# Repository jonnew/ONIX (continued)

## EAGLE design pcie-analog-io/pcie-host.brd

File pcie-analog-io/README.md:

# analog IO card

This board roughly conforms the PCIe card mechanical standard and uses a flex
FMC cable to connect to the master FPGA module. This board performs all
communication over FMC -- the PCIe slot design is for mechanical support and to
provide a common and standardized mounting solution across acquisition PCs

### Features

- 16 chs ADC
- 16 chs DAC
- Digital io

### Pinout

Conform to standard NI high density VHDCI pinouts to enable the use of existing cables and breakout boxes

### BOM

#### ADC

AD7616BSTZ-ND

http://www.ti.com/lit/ds/symlink/ads7950.pdf

http://www.analog.com/en/products/analog-to-digital-converters/precision-adc-20msps/simultaneous-sampling-ad-converters/ad7617.html?doc=AD7617.pdf

#### DAC

http://www.analog.com/en/products/digital-to-analog-converters/precision-dac/bipolar-da-converters/ad5767.html

http://www.analog.com/en/products/digital-to-analog-converters/precision-dac/bipolar-da-converters/ad5767.html

LTC2668CUJ-12#PBF-ND

296-25558-1-ND

#### Isolation
I dont think this is needed

#### LVDS to single ended

#### Connector

We can use Molex dual/stacked Ultra+(tm) VHDCI plugs
http://www.molex.com/molex/products/family?key=ultra__vhdci&channel=products&chanName=family&pageTitle=Introduction&parentKey=shielded_input_output_io

We likely have enough space to fit two of these on there (~44mm width each) 

## Manufacturing requirements

TODO:
- PCB thickness:
- 4 layers
- 8mil trace width & spacing
- 12mil min. drill

PCI Brackets:
http://www.mouser.com/Search/ProductDetail.aspx?R=9203virtualkey53400000virtualkey534-9203
http://www.cbttechnology.com/products/s/PCI/PCI-blanks-database.php
http://www.keyelco.com/category.cfm/Standard-Blanks/Computer-Bracket-Blanks-With-Tabs/p/427/id/704/c_id/899

There is one 0.05" pitch BGA connector (the samtech FMC connector) and a few omnetics connectors with inacessible pins on the board, so a stencil and reflow soldering need to be used.

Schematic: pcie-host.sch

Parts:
C1: 1uF; 0603
C2, C5, C6, C7, C8, C9, C17, C25, C39, C40, C49, C50, C51, C52, C53, C54, C55, C56, C57, C58, C59, C60, C61, C80, C81, C82, C84, C86, C88, C91, C92, C93, C95, C97: 0.1uF; 0603
C3, C13: 4.7uF; 0805
C4: 10uF; 0603
C10, C11, C26, C27, C28, C30, C31, C32, C33: 10nF; 0402
C12: 47nF; 0402
C14, C15, C16, C23, C29, C34, C35, C36, C37: 0.1uF; 0402
C18, C22, C38: 4.7uF; 1206
C19: 4.7F; 1206
C20: 1uF; 0805
C21, C24: 22uF; 1206
C42, C45: 10uF; 1206
C44: 100uF; 153CLV-0807
C46: 47uF; 153CLV-0807
C47, C48, C66, C87: 22uF; 1210-POL
C83, C85, C89, C90, C94, C96, C98: 1nF; 0402
D1, D2, D3, D4: BAR66; SOT23
D5: LM4040D25FTA; SOT23
D6: KDZ4.3B; SOD123
DI1, DI2: SMA002; SMA_JACK_CONREVSMA002-G
DO1, DO2: SMA002; SMA_JACK_CONREVSMA002-G
F1, F2, F3, F4: C014F-2; 1812
FMC_LPC: FMC_LPC_160_PIN; FMC_LPC_MALE_WITH_SP601_BSILK
L1: 1008PS-472KLB; 1008PS
L2: SRN6045TA-101M; SRN6045TA
L3: MPZ2012S102AT000; 0805
L4, L5, L6: BLM18KG601SN1D; 0603
L7/0R: 74438356010; 4020
LINK: SMA002; SMA_JACK_CONREVSMA002-G
OUT: 569-011x; 569-011X-X00_LED_ARRAY
PCIE-PWR: 0455580003; PCIE-POWER-6PIN
PWR/LOCK: 569-011x; 569-011X-X00_LED_ARRAY
Q1, Q2, Q5: NDS351AN; SOT23-GSD
Q3, Q4: BSH103; SOT23-GSD
R1, R2, R9, R11, R33, R46, R65, R66, R71, R72, R73, R74, R75: 1k; 0603
R3, R4, R8, R10, R34: 100k; 0603
R5, R6, R31, R32, R69, R70: 2.2k; 0603
R7, R20: 1K; 0603
R12, R13: 4.7k; 0603
R14, R15, R18, R19, R25, R57, R60, R62: 10K; 0402
R16, R17, R21, R22, R23, R24: 150,0.25W; 1206
R26, R27, R56: 10k; 0603
R28, R29, R67: 100; 0603
R30: 49.9; 0402
R35, R36, R37, R38, R39, R40, R41, R42, R43, R44, R45, R47, R48, R49, R50, R51, R52, R53, R54: 22; 0402
R55: 30.1k; 0603
R58, R61, R63: 0; 0402
R59: 13.3k; 0603
R64: 649k; 0603
R68: 9.53k; 0603
TERM: 569-011x; 569-011X-X00_LED_ARRAY
TP1, TP18, TP19, TP20, TP28: GND(ISO); TESTPOINT_1MM
TP2: +1.8V(ISO); TESTPOINT_1MM
TP3: +3.3V(ISO); TESTPOINT_2MM
TP4: +5.5V(ISO); TESTPOINT_2MM
TP5: PASS; TP06R
TP6: DI1; TP09SQ
TP7: DI0; TP09SQ
TP8: GND; TESTPOINT_0.035IN
TP9: VPROTECT(+4.3V); TESTPOINT_0.035IN
TP10, TP14, TP15, TP16, TP17, TP21: GND; TESTPOINT_2MM
TP11, TP22: +3.3V; TESTPOINT_2MM
TP12: +12V(FPGA); TESTPOINT_2MM
TP13: +12V(ATX); TESTPOINT_2MM
TP23: GND; TESTPOINT_1MM
TP24: SDA; TESTPOINT_1MM
TP25: SCL; TESTPOINT_1MM
TP26: SCL(ISO); TESTPOINT_1MM
TP27: SDA(ISO); TESTPOINT_1MM
TP29: GPIO3; TP06R
U1: ISO; SCREW4
U2, U3: JP3E; JP3
U4: SN74LVT125; SO14
U5, U6: ADCMP600; SOT-23-5
U7: DIPSW-004_SMD-0.05IN; DIP04-SMD
U8: MCP47FEBX2; TSSOP-8
U9: DS90UB914A-Q1; WQFN48
U10: LTM4622_BGA; BGA_5X5_625X625
U11: ISO1540DR; SOIC127P500X400-8N
U12: UEI15-050-Q12P-C; UEI15
U13, U14, U15, U16: ISO7240M; SOIC_WIDE_16
U17: ISO7242M; SOIC_WIDE_16
U18: COMM; SCREW4
U19: SN65LVDT388A; TSSOP-38
U20: SN65LVDS387; TSSOP-64
U21: SN65LVDS391; TSSOP-16
U$2: MOLEX_DUAL_STACKED_VHDCI; MOLEX_743370911_SD_DUAL_STACKED_VHDCI
X1: PCI-MECH_STD-H_HALF-W_FMC-STRAIN; PCI-ADDIN_STD-H_HALF-L_FMC-STRAIN

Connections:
2V5_REF: D5.1 (C), R67.1, U2.3, U3.3
$N1: D4.3 (COMM), F2.2, R6.2, R17.2, R22.2, R24.2, R29.1
$N2: D2.3 (COMM), F4.2, R12.2, U4.8 (3Y), U4.11 (4Y)
$N3: D3.3 (COMM), F1.2, R5.2, R16.2, R21.2, R23.2, R28.1
$N101: D1.3 (COMM), F3.2, R13.2, U4.3 (1Y), U4.6 (2Y)
+1V8_ISO: C24.2, C31.2, C32.2, C33.2, C35.2, C36.2, C37.2, L4.2, L5.2, L6.1, R57.1, R60.1, R62.1, TP2.1, U1.2, U9.3 (VDDSSCG), U9.17 (VDDD), U9.36 (VDDR), U10.D1 (VOUT1), U10.E1 (VOUT1)
+3V3: C1.2, C2.2, C8.1, C9.1, C20.2, C25.2, C56.2, C57.2, C58.2, C59.2, C60.2, C61.2, C81.2, C83.2, C84.2, C85.2, C86.2, C87.+, C88.2, C89.2, C90.2, C91.2, C92.2, C93.2, C94.2, C95.2, C96.2, C97.2, C98.2, FMC_LPC.P$116 (3P3V2), FMC_LPC.P$118 (3P3V3), FMC_LPC.P$120 (3P3V4), FMC_LPC.P$159 (3P3V1), R1.2, R2.2, R31.2, R32.2, R67.2, R71.2, R72.2, TP11.1, TP22.1, U4.14 (VCC), U5.5 (V+), U6.5 (V+), U8.1 (VDD), U8.2 (REFA), U11.1 (VDD1), U13.P10 (EN2), U13.P16 (VDD2), U14.P10 (EN2), U14.P16 (VDD2), U15.P10 (EN2), U15.P16 (VDD2), U16.P10 (EN2), U16.P16 (VDD2), U17.P10 (EN2), U17.P16 (VDD2), U18.2, U19.21 (VCC), U19.22 (END), U19.25 (ENC), U19.29 (DVCC), U19.33 (ENB), U19.36 (ENA), U19.37 (VCC), U20.2 (VCC), U20.3 (VCC), U20.5 (ENA), U20.10 (ENB), U20.16 (VCC), U20.17 (VCC), U20.23 (ENC), U20.28 (END), U20.30 (VCC), U20.31 (VCC), U21.1 (EN1,2), U21.4 (VCC), U21.8 (EN3,4)
+3V3_ISO: C21.2, C27.2, C28.2, C29.2, C30.2, C34.2, C38.2, C49.2, C50.2, C51.2, C52.2, C53.2, C54.2, R14.2, R15.2, R18.2, R19.2, R25.1, R46.2, R65.2, R66.2, R75.2, TP3.1, U1.3, U9.7 (VDDIO3), U9.20 (VDDIO2), U9.29 (VDDIO1), U10.A1 (VOUT2), U10.B1 (VOUT2), U11.8 (VDD2), U13.P1 (VDD1), U14.P1 (VDD1), U15.P1 (VDD1), U16.P1 (VDD1), U17.P1 (VDD1)
+3V3_ISO_PG: U16.P11 (VOD), U20.27 (D4A)
+3V3_ISO_PG_ISO: R56.2, U10.D4 (PGOOD1), U16.P6 (VID)
+3V3_ISO_PG_N: FMC_LPC.P$89 (LA01_N_CC), U20.33 (D4Z)
+3V3_ISO_PG_P: FMC_LPC.P$88 (LA01_P_CC), U20.34 (D4Y)
+5.5V_ISO: C13.2, C17.1, C42.2, C45.2, C47.+, C48.+, L3.1, TP4.1, U10.A2 (VIN), U10.B2 (RUN2), U10.B3 (VIN), U10.D2 (RUN1), U10.D3 (VIN), U10.E2 (VIN), U12.3 (+VO)
+12V_ATX: C44.+, C46.+, L7/0R.1, PCIE-PWR.1, PCIE-PWR.2, PCIE-PWR.3, TP13.1
+12V_FPGA: C66.+, C80.2, C82.2, FMC_LPC.P$155 (12P0V1), FMC_LPC.P$157 (12P0V2), R69.2, R70.2, TP12.1, U18.3
BIAS_DI0: U2.1, U8.3 (VOUT0)
BIAS_DI1: U3.1, U8.4 (VOUT1)
BISTEN: R19.1, U7.1, U9.6 (BISTEN)
D0: U13.P14 (VOA), U20.6 (A1A)
D0_ISO: R54.1, U13.P3 (VIA)
D0_N: FMC_LPC.P$98 (LA13_N), U20.63 (A1Z)
D0_P: FMC_LPC.P$97 (LA13_P), U20.64 (A1Y)
D1: U13.P13 (VOB), U20.7 (A2A)
D1_ISO: R38.1, U13.P4 (VIB)
D1_N: FMC_LPC.P$17 (LA11_N), U20.61 (A2Z)
D1_P: FMC_LPC.P$16 (LA11_P), U20.62 (A2Y)
D2: U13.P12 (VOC), U20.8 (A3A)
D2_ISO: R45.1, U13.P5 (VIC)
D2_N: FMC_LPC.P$56 (LA12_N), U20.59 (A3Z)
D2_P: FMC_LPC.P$55 (LA12_P), U20.60 (A3Y)
D3: U13.P11 (VOD), U20.9 (A4A)
D3_ISO: R53.1, U13.P6 (VID)
D3_N: FMC_LPC.P$135 (LA10_N), U20.57 (A4Z)
D3_P: FMC_LPC.P$134 (LA10_P), U20.58 (A4Y)
D4: U14.P14 (VOA), U20.11 (B1A)
D4_ISO: R37.1, U14.P3 (VIA)
D4_N: FMC_LPC.P$95 (LA09_N), U20.55 (B1Z)
D4_P: FMC_LPC.P$94 (LA09_P), U20.56 (B1Y)
D5: U14.P13 (VOB), U20.12 (B2A)
D5_ISO: R44.1, U14.P4 (VIB)
D5_N: FMC_LPC.P$14 (LA07_N), U20.53 (B2Z)
D5_P: FMC_LPC.P$13 (LA07_P), U20.54 (B2Y)
D6: U14.P12 (VOC), U20.13 (B3A)
D6_ISO: R52.1, U14.P5 (VIC)
D6_N: FMC_LPC.P$53 (LA08_N), U20.51 (B3Z)
D6_P: FMC_LPC.P$52 (LA08_P), U20.52 (B3Y)
D7: U14.P11 (VOD), U20.14 (B4A)
D7_ISO: R36.1, U14.P6 (VID)
D7_N: FMC_LPC.P$92 (LA05_N), U20.49 (B4Z)
D7_P: FMC_LPC.P$91 (LA05_P), U20.50 (B4Y)
D8: U15.P14 (VOA), U20.19 (C1A)
D8_ISO: R43.1, U15.P3 (VIA)
D8_N: FMC_LPC.P$11 (LA04_N), U20.47 (C1Z)
D8_P: FMC_LPC.P$10 (LA04_P), U20.48 (C1Y)
D9: U15.P13 (VOB), U20.20 (C2A)
D9_ISO: R51.1, U15.P4 (VIB)
D9_N: FMC_LPC.P$131 (LA06_N), U20.45 (C2Z)
D9_P: FMC_LPC.P$130 (LA06_P), U20.46 (C2Y)
D10: U15.P12 (VOC), U20.21 (C3A)
D10_ISO: R35.1, U15.P5 (VIC)
D10_N: FMC_LPC.P$50 (LA03_N), U20.43 (C3Z)
D10_P: FMC_LPC.P$49 (LA03_P), U20.44 (C3Y)
D11: U15.P11 (VOD), U20.22 (C4A)
D11_ISO: R42.1, U15.P6 (VID)
D11_N: FMC_LPC.P$8 (LA02_N), U20.41 (C4Z)
D11_P: FMC_LPC.P$7 (LA02_P), U20.42 (C4Y)
DAC_LAT: U8.6 (LAT/HVC), U19.32 (B1Y)
DAC_LAT_N: FMC_LPC.P$20 (LA15_N), U19.7 (B1B)
DAC_LAT_P: FMC_LPC.P$19 (LA15_P), U19.6 (B1A)
DI0: TP7.TP, U5.1 (OUT), U21.2 (1A)
DI0_N: FMC_LPC.P$68 (LA25_N), U21.15 (1Z)
DI0_P: FMC_LPC.P$67 (LA25_P), U21.16 (1Y)
DI0_TERM: R9.1, R73.1, U19.35 (A1Y)
DI0_TERM_N: FMC_LPC.P$139 (LA1N_N), U19.2 (A1B)
DI0_TERM_P: FMC_LPC.P$138 (LA14_P), U19.1 (A1A)
DI1: TP6.TP, U6.1 (OUT), U21.3 (2A)
DI1_N: FMC_LPC.P$29 (LA24_N), U21.13 (2Z)
DI1_P: FMC_LPC.P$28 (LA24_P), U21.14 (2Y)
DI1_TERM: R11.1, R74.1, U19.34 (A2Y)
DI1_TERM_N: FMC_LPC.P$59 (LA16_N), U19.4 (A2B)
DI1_TERM_P: FMC_LPC.P$58 (LA16_P), U19.3 (A2A)
DO0: U4.2 (1A), U4.5 (2A), U19.26 (C2Y)
DO0_N: FMC_LPC.P$143 (LA18_N_CC), U19.12 (C1B)
DO0_P: FMC_LPC.P$142 (LA18_P_CC), U19.11 (C1A)
DO1: U4.9 (3A), U4.12 (4A), U19.27 (C1Y)
DO1_N: FMC_LPC.P$62 (LA20_N), U19.14 (C2B)
DO1_P: FMC_LPC.P$61 (LA20_P), U19.13 (C2A)
DOUTP_F: C16.2, L1.2, LINK.CLK (1), R7.2
DO_TEST: U19.31 (B2Y)
DO_TEST_N: FMC_LPC.P$101 (LA17_N_CC), U19.9 (B2B)
DO_TEST_P: FMC_LPC.P$100 (LA17_P_CC), U19.8 (B2A)
GND: C1.1, C2.1, C6.2, C7.2, C8.2, C9.2, C20.1, C25.1, C44.-, C46.-, C55.1, C56.1, C57.1, C58.1, C59.1, C60.1, C61.1, C66.-, C80.1, C81.1, C82.1, C83.1, C84.1, C85.1, C86.1, C87.-, C88.1, C89.1, C90.1, C91.1, C92.1, C93.1, C94.1, C95.1, C96.1, C97.1, C98.1, D1.1 (A), D2.1 (A), D3.1 (A), D4.1 (A), D5.2 (A), D6.A, DI1.GND$1 (2), DI1.GND$2 (2), DI1.GND$3 (2), DI1.GND$4 (2), DI2.GND$1 (2), DI2.GND$2 (2), DI2.GND$3 (2), DI2.GND$4 (2), DO1.GND$1 (2), DO1.GND$2 (2), DO1.GND$3 (2), DO1.GND$4 (2), DO2.GND$1 (2), DO2.GND$2 (2), DO2.GND$3 (2), DO2.GND$4 (2), FMC_LPC.GNDA (GND), FMC_LPC.GNDB (GND), FMC_LPC.P$3 (GND), FMC_LPC.P$6 (GND), FMC_LPC.P$9 (GND), FMC_LPC.P$12 (GND), FMC_LPC.P$15 (GND), FMC_LPC.P$18 (GND), FMC_LPC.P$21 (GND), FMC_LPC.P$24 (GND), FMC_LPC.P$27 (GND), FMC_LPC.P$30 (GND), FMC_LPC.P$33 (GND), FMC_LPC.P$36 (GND), FMC_LPC.P$39 (GND), FMC_LPC.P$41 (GND), FMC_LPC.P$44 (GND), FMC_LPC.P$45 (GND), FMC_LPC.P$48 (GND), FMC_LPC.P$51 (GND), FMC_LPC.P$54 (GND), FMC_LPC.P$57 (GND), FMC_LPC.P$60 (GND), FMC_LPC.P$63 (GND42), FMC_LPC.P$66 (GND), FMC_LPC.P$69 (GND), FMC_LPC.P$72 (GND), FMC_LPC.P$75 (GND), FMC_LPC.P$78 (GND), FMC_LPC.P$80 (GND), FMC_LPC.P$82 (GND), FMC_LPC.P$83 (GND), FMC_LPC.P$86 (GND), FMC_LPC.P$87 (GND), FMC_LPC.P$90 (GND), FMC_LPC.P$93 (GND), FMC_LPC.P$96 (GND), FMC_LPC.P$99 (GND), FMC_LPC.P$102 (GND), FMC_LPC.P$105 (GND), FMC_LPC.P$108 (GND), FMC_LPC.P$117 (GND), FMC_LPC.P$119 (GND), FMC_LPC.P$121 (GND), FMC_LPC.P$124 (GND), FMC_LPC.P$125 (GND), FMC_LPC.P$128 (GND), FMC_LPC.P$129 (GND), FMC_LPC.P$132 (GND), FMC_LPC.P$133 (GND), FMC_LPC.P$136 (GND), FMC_LPC.P$137 (GND), FMC_LPC.P$140 (GND), FMC_LPC.P$141 (GND), FMC_LPC.P$144 (GND), FMC_LPC.P$145 (GND), FMC_LPC.P$148 (GND), FMC_LPC.P$149 (GND), FMC_LPC.P$152 (GND), FMC_LPC.P$153 (GND), FMC_LPC.P$156 (GND), FMC_LPC.P$158 (GND19), FMC_LPC.P$160 (GND), PCIE-PWR.4, PCIE-PWR.5, PCIE-PWR.6, Q1.S, Q2.S, Q3.S, Q4.S, R3.1, R4.1, R5.1, R6.1, R8.1, R10.1, TERM.C1 (C), TERM.C2 (C), TP8.1, TP10.1, TP14.1, TP15.1, TP16.1, TP17.1, TP21.1, TP23.1, U4.7 (GND), U5.2 (V-), U6.2 (V-), U8.5 (AVSS), U11.4 (GND1), U12.2 (GND), U13.P9 (GND2), U13.P15 (GND2), U14.P9 (GND2), U14.P15 (GND2), U15.P9 (GND2), U15.P15 (GND2), U16.P9 (GND2), U16.P15 (GND2), U17.P9 (GND2), U17.P15 (GND2), U18.1, U18.4, U19.5 (AGND), U19.10 (AGND), U19.15 (AGND), U19.20 (GND), U19.28 (DGND), U19.30 (DGND), U19.38 (GND), U20.1 (GND), U20.4 (GND), U20.15 (GND), U20.18 (GND), U20.29 (GND), U20.32 (GND), U21.5 (GND)
GND_ISO: C3.1, C4.1, C5.2, C10.1, C11.1, C13.1, C14.1, C15.1, C17.2, C18.1, C19.1, C21.1, C22.1, C23.1, C24.1, C26.1, C27.1, C28.1, C29.1, C30.1, C31.1, C32.1, C33.1, C34.1, C35.1, C36.1, C37.1, C38.1, C39.1, C40.1, C42.1, C45.1, C47.-, C48.-, C49.1, C50.1, C51.1, C52.1, C53.1, C54.1, LINK.GND$1 (2), LINK.GND$2 (2), LINK.GND$3 (2), LINK.GND$4 (2), PWR/LOCK.C1 (C), Q5.S, R30.2, R34.1, R55.2, R58.2, R59.2, R61.2, R63.2, R64.2, R68.2, TP1.1, TP18.1, TP19.1, TP20.1, TP28.1, U1.1, U1.4, U7.5, U7.6, U7.7, U7.8, U9.43 (RES), U9.44 (TESTEN), U9.49 (DAP), U10.B5 (GND), U10.C1 (GND), U10.C2 (GND), U10.C5 (SYNC/MODE), U10.D5 (GND), U11.5 (GND2), U12.5 (-VO), U13.P2 (GND1), U13.P8 (GND1), U14.P2 (GND1), U14.P8 (GND1), U15.P2 (GND1), U15.P8 (GND1), U16.P2 (GND1), U16.P8 (GND1), U17.P2 (GND1), U17.P8 (GND1)
GPI0: U17.P13 (VOB), U21.7 (4A)
GPI0_ISO: R40.1, U17.P4 (VIB)
GPI0_N: FMC_LPC.P$26 (LA21_N), U21.9 (4Z)
GPI0_P: FMC_LPC.P$25 (LA21_P), U21.10 (4Y)
GPI1: U17.P14 (VOA), U21.6 (3A)
GPI1_ISO: R48.1, U17.P3 (VIA)
GPI1_N: FMC_LPC.P$104 (LA23_N), U21.11 (3Z)
GPI1_P: FMC_LPC.P$103 (LA23_P), U21.12 (3Y)
GPO0: U17.P11 (VID), U19.24 (D1Y)
GPO0_N: FMC_LPC.P$23 (LA19_N), U19.17 (D1B)
GPO0_P: FMC_LPC.P$22 (LA19_P), U19.16 (D1A)
GPO1: U17.P12 (VIC), U19.23 (D2Y)
GPO1_ISO: R47.1, U17.P5 (VOC)
GPO1_N: FMC_LPC.P$65 (LA22_N), U19.19 (D2B)
GPO1_P: FMC_LPC.P$64 (LA22_P), U19.18 (D2A)
HSYNC: U16.P14 (VOA), U20.24 (D1A)
HSYNC_ISO: R50.1, U16.P3 (VIA)
HSYNC_N: FMC_LPC.P$85 (GBTCLK0_M2C_N), U20.39 (D1Z)
HSYNC_P: FMC_LPC.P$84 (GBTCLK0_M2C_P), U20.40 (D1Y)
IDX0: R57.2, R58.1, U9.35 (IDX0)
IDX1: R60.2, R61.1, U9.34 (IDX1)
INTVCC: R56.1, U10.C3 (INTVCC)
LOCK: R33.2, U9.48 (LOCK)
MODE: R62.2, R63.1, U9.37 (MODE)
unnamed: R39.1, U17.P6 (VOD)
unnamed: Q3.D, R16.1, R21.1, R23.1
unnamed: R28.2, U5.3 (+IN)
unnamed: R49.2, U9.8 (PCLK)
unnamed: R59.1, U10.A4 (FB2)
unnamed: DI2.CLK (1), F2.1
unnamed: Q4.D, R17.1, R22.1, R24.1
unnamed: C39.2, U10.A3 (TRACK/SS2)
unnamed: R11.2, TERM.A1 (A)
unnamed: R55.1, U10.E4 (FB1)
unnamed: DI1.CLK (1), F1.1
unnamed: C40.2, U10.E3 (TRACK/SS1)
unnamed: R41.2, U9.9 (VSYNC)
unnamed: DO1.CLK (1), F3.1
unnamed: PWR/LOCK.A2 (A), R46.1
unnamed: R50.2, U9.10 (HSYNC)
unnamed: DO2.CLK (1), F4.1
unnamed: C6.1, R26.2, U5.4 (-IN)
unnamed: R29.2, U6.3 (+IN)
unnamed: C7.1, R27.2, U6.4 (-IN)
unnamed: L1.1, L2.2, R7.1, R20.2
unnamed: C3.2, C5.1, L2.1, L3.2, R20.1
unnamed: OUT.A1 (A), R1.1
unnamed: R31.1, U4.1 (~1G), U4.4 (~2G)
unnamed: R32.1, U4.10 (~3G), U4.13 (~4G)
unnamed: R68.1, U12.4 (TRIM)
unnamed: C16.1, U9.41 (RIN0+)
unnamed: C12.1, U9.42 (RIN0-)
unnamed: PWR/LOCK.C2 (C), Q5.D
unnamed: R9.2, TERM.A2 (A)
unnamed: OUT.A2 (A), R2.1
unnamed: C12.2, R30.1
unnamed: PWR/LOCK.A1 (A), R75.1
unnamed: Q4.G, R8.2, R74.2
unnamed: OUT.C1 (C), Q1.D
unnamed: R27.1, U3.2
unnamed: Q3.G, R10.2, R73.2
unnamed: TP29.TP, U9.25 (GPIO3)
unnamed: Q1.G, R3.2, R13.1
unnamed: R51.2, U9.13 (ROUT9)
unnamed: R43.2, U9.14 (ROUT8)
unnamed: R36.2, U9.15 (ROUT7)
unnamed: R52.2, U9.16 (ROUT6)
unnamed: R44.2, U9.18 (ROUT5)
unnamed: R37.2, U9.19 (ROUT4)
unnamed: R53.2, U9.21 (ROUT3)
unnamed: R45.2, U9.22 (ROUT2)
unnamed: R38.2, U9.23 (ROUT1)
unnamed: R54.2, U9.24 (ROUT0)
unnamed: R42.2, U9.11 (ROUT11)
unnamed: R35.2, U9.12 (ROUT10)
unnamed: R47.2, U9.26 (GPIO2)
unnamed: R40.2, U9.27 (GPIO1)
unnamed: R48.2, U9.28 (GPIO0)
unnamed: OUT.C2 (C), Q2.D
unnamed: Q2.G, R4.2, R12.1
unnamed: Q5.G, R33.1, R34.2
unnamed: R26.1, U2.2
unnamed: R64.1, U10.C4 (FREQ)
OEN: R15.1, U7.2, U9.5 (OEN)
OSS_SEL: R18.1, U7.3, U9.4 (OSS_SEL)
PASS: R39.2, TP5.TP, U9.47 (PASS)
PCLK: U16.P12 (VOC), U20.26 (D3A)
PCLK_ISO: R49.1, U16.P5 (VIC)
PCLK_N: FMC_LPC.P$43 (CLK1_M2C_N), U20.35 (D3Z)
PCLK_P: FMC_LPC.P$42 (CLK1_M2C_P), U20.36 (D3Y)
PDN: C4.2, R25.2, U9.30 (PDN)
SCL: FMC_LPC.P$150 (SCL), R72.1, TP25.1, U8.7 (SCL), U11.3 (SCL1)
SCL_ISO: R65.1, TP26.1, U9.2 (SCL), U11.6 (SCL2)
SDA: FMC_LPC.P$151 (SDA), R71.1, TP24.1, U8.8 (SDA), U11.2 (SDA1)
SDA_ISO: R66.1, TP27.1, U9.1 (SDA), U11.7 (SDA2)
SEL: R14.1, U7.4, U9.46 (SEL)
TDI-TDO: FMC_LPC.P$110 (TDI), FMC_LPC.P$111 (TDO)
VDDCML0: C11.2, C15.2, C19.2, L5.1, U9.40 (VDDCML0)
VDDCML1: C10.2, C14.2, C18.2, L4.1, U9.31 (VDDCML1)
VDDPLL: C22.2, C23.2, C26.2, L6.2, U9.45 (VDDPLL)
VIN: L7/0R.2, U12.1 (VIN), U12.6 (EN)
VSYNC: U16.P13 (VOB), U20.25 (D2A)
VSYNC_ISO: R41.1, U16.P4 (VIB)
VSYNC_N: FMC_LPC.P$5 (CLK0_M2C_N), U20.37 (D2Z)
VSYNC_P: FMC_LPC.P$4 (CLK0_M2C_P), U20.38 (D2Y)
V_PROTECT: C55.2, D1.2 (C), D2.2 (C), D3.2 (C), D4.2 (C), D6.C, R69.1, R70.1, TP9.1

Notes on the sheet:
HEADSTAGE SIDE
AQ. BOARD SIDE
ISOLATED TEST POINTS
POWER INPUT
FMC HEADER
PCI ADD IN CARD
INPUT PROTECTION BIAS VOLTAGE ~4.6V
IMMEDIATE INPUT OVERVOLTAGE PROTECTION
NOTES: - ISO7240 Zo for 3.3V is ~100 Ohms.
L2 is the smallest package size I could find that barely meets current saturation requriements. An 8x8mm device that is probably safer is the Bourns SRN8040TA series.
UEI15 Choices: 12V: S24SE12002 w/ Rtrim = Inf 5.5V: UEI15-050-Q12P-C w/ Rtrm = 9.53k resistor
Power: ~1.3A DC at 12V; 15.6W. With 90% efficiency regulation to 5.5V at serializer, this translates to 2.55A available, which is enough for 1A/LED + 500 mA serializer and FPGA.
LVCMOS1.8
Seeed 4 layer stackup: 1.4 mil trace 8 mill prepeg 0.7 mil trace XX mil FR4 core 0.7 mil trace 8 mil prepeg 1.4 mil trace
SN65LVDT388A has integrated 110 ohm term resistors.
Parity error on high-speed forward channel and pass will go low. This should be provided to LPC connector

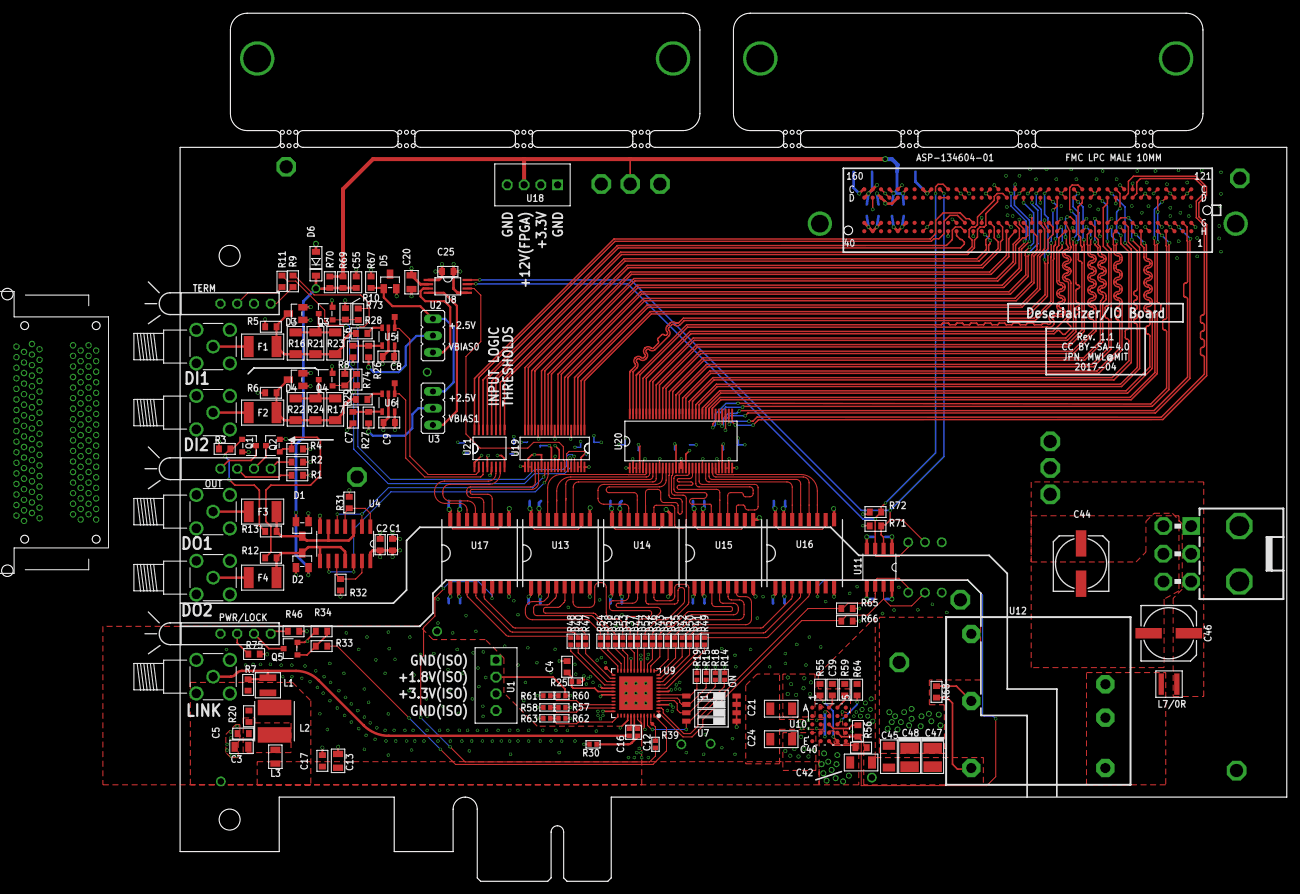
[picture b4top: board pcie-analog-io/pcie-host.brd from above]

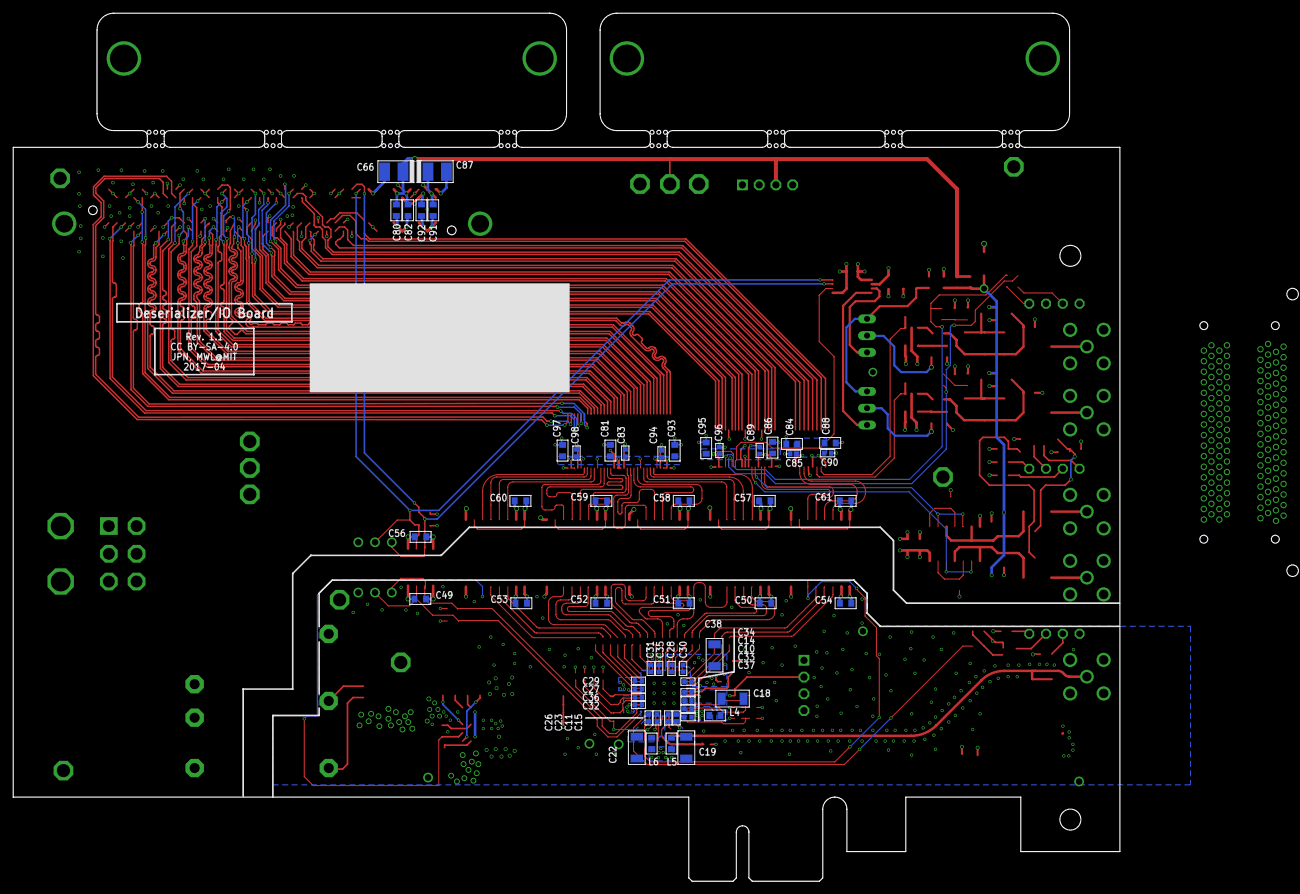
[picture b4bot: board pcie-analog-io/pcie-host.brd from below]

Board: 4 copper layers, 167.6 x 131.5 mm, 238 parts (57 on the bottom side), 198 nets.

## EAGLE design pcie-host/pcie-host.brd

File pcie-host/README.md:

# PCIe Host Board
This card serves as host interface for serialized headstages. It is really just
a digital breakout for the FMC connector on the KC705 board. This board
roughly conforms the PCIe card mechanical standard and uses a flex FMC cable to
connect to the master FPGA module. This board performs all communication over
FMC. The PCIe slot design is for mechanical support and to provide a common and
standardized mounting solution across acquisition PCs

## Gerber Files
{% include gerber_layers.md %}

### Bill of Materials
The bill of materials for this device can be found
[here](https://docs.google.com/spreadsheets/d/18WfmbLGt8bGUUdksKp6AKA_wMX2SJ3Tndin-nnEgUCs/edit?usp=sharing).

## Manufacturing Requirements
In order to meet approximately correct trace impedances, the design further is
assuming the following stackup:

### Pinout
FMC LPC pinout can be found
[here](https://docs.google.com/spreadsheets/d/18WfmbLGt8bGUUdksKp6AKA_wMX2SJ3Tndin-nnEgUCs/edit#gid=584734392)

## Future Direction
Eventually, we hope to integrate this board and the KC705 into a single board.
This board will allow VITA-57 compliant IO modules for communication with
headstages and external equipment. Alternatively, we may make this board into a
VITA-57 compliant daughter card to interface with existing PCIe breakouts (e.g.
the [Numato
Nereid](https://numato.com/product/nereid-kintex-7-pci-express-fpga-development-board))

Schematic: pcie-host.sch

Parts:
C1, C2, C3, C4, C6, C7, C9, C10, C13, C14, C16, C17, C18, C25, C27, C29, C30, C32, C33, C42, C44, C46, C48, C49, C59, C60, C62, C63, C70, C71, C72, C74, C76, C77, C80, C81: 0.1uF; 0603
C5, C8, C23, C24: 22uF; 1210-POL
C11: 47uF; 153CLV-0807
C12, C15: 1uF; 0805
C19, C20: 22uF; 1206
C21: 100uF; 153CLV-0807
C22, C31, C61: 10uF; 1206
C26, C28, C43, C45, C47, C73, C75: 1nF; 0402
C34, C36, C41, C50, C52, C55, C64, C65, C68: 10nF; 0402
C35, C37, C40, C51, C53, C56, C57, C66, C69: 0.1uF; 0402
C38, C39, C54, C67, C78, C79: 4.7uF; 1206
C58: 47nF; 0402
D1, D2, D3, D4: BAR66; SOT23
D5: LM4040D25FTA; SOT23
D6: KDZ4.3B; SOD123
DI1, DI2: SMA002; SMA_JACK_CONREVSMA002-G
DO1, DO2: SMA002; SMA_JACK_CONREVSMA002-G
F1, F2, F3, F4: C014F-2; 1812
FMC_LPC: FMC_LPC_160_PIN; FMC_LPC_MALE_WITH_SP601_BSILK
J1, J2: JP3E; JP3
J3: COMM; SCREW4
J4: ISO; 1X04
J5, J6, J7, J8: COAX_SMA-VERT-SMA; SMA_VERT
L1, L2, L3: BLM18KG601SN1D; 0603
L4: MPZ2012S102AT000; 0805
L5: 1008PS-472; 1008PS
L6: SRNxx-101M; SRN6045TA
L7/0R: 74438356010; 4020
LINK: SMA002; SMA_JACK_CONREVSMA002-G
OUT: 569-011x; 569-011X-X00_LED_ARRAY
PCIE-PWR: 0455580003; PCIE-POWER-6PIN
PWR/LOCK: 569-011x; 569-011X-X00_LED_ARRAY
Q1, Q2: BSH103; SOT23-GSD
Q3, Q4, Q6: NDS351AN; SOT23-GSD
Q5: NDS351; SOT23-GSD
R1, R10, R27: 100; 0603
R2, R11, R21, R22, R24, R25: 2.2k; 0603
R3, R12, R34: 10k; 0603
R4, R5, R6, R13, R14, R15: 150,0.25W; 1206
R7, R8, R16, R17, R20, R28, R30, R31, R32, R33, R36, R64, R66, R68, R70, R71: 1k; 0603
R9, R18, R23, R29, R67, R69: 100k; 0603
R19, R26: 4.7k; 0603
R35: 9.53k; 0603
R37: 30.1k; 0603
R38: 649k; 0603
R39: 13.3k; 0603
R40, R41, R43, R44, R45, R46, R47, R48, R49, R50, R51, R52, R53, R54, R55, R57, R58, R59, R60, R78: 22; 0402
R42: 49.9; 0402
R56, R61, R62, R63, R65, R72, R73, R74: 10k; 0402
R75, R76, R79, R80: 0; 0402
R77: 3k; 0402
S1: SPST_TACT2_EVQPF; EVQPF
TERM: 569-011x; 569-011X-X00_LED_ARRAY
TP1: DI1; TP09SQ
TP2: DI0; TP09SQ
TP3: GND; TESTPOINT_0.035IN
TP4, TP5, TP6, TP7, TP8, TP9: GND; TESTPOINT_2MM
TP10, TP11: +3.3V; TESTPOINT_2MM
TP12: +12V(FPGA); TESTPOINT_2MM
TP13: +12V(ATX); TESTPOINT_2MM
TP14: VPROTECT(+4.3V); TESTPOINT_0.035IN
TP15: SCL(ISO); TESTPOINT_1MM
TP16: SDA(ISO); TESTPOINT_1MM
TP17, TP21, TP25, TP26: GND(ISO); TESTPOINT_1MM
TP18: GND; TESTPOINT_1MM
TP19: SDA; TESTPOINT_1MM
TP20: SCL; TESTPOINT_1MM
TP22: +1.8V(ISO); TESTPOINT_1MM
TP23: +3.3V(ISO); TESTPOINT_2MM
TP24: +5.5V(ISO); TESTPOINT_2MM
U1, U2: ADCMP600; SOT-23-5
U3: SN74LVT125; SO14
U4: MCP47FEBX2; TSSOP-8
U5: ISO1540DR; SOIC127P500X400-8N
U6: UEI15-050-Q12P-C; UEI15
U7: LTM4622_BGA; BGA_5X5_625X625
U8: SN65LVDT388A; TSSOP-38
U9, U10, U13, U14, U17: ISO7740; SOIC_WIDE_16
U11: SN65LVDS387; TSSOP-64
U12: DS90UB914A-Q1; WQFN48
U15: DIPSW-004_SMD-0.05IN; DIP04-SMD
U16: SN65LVDS391; TSSOP-16
U18: ISO7741; SOIC_WIDE_16
X1: PCI-MECH_STD-H_HALF-W_FMC-STRAIN; PCI-ADDIN_STD-H_HALF-L_FMC-STRAIN

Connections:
2V5_REF: D5.1 (C), J1.3, J2.3, R27.1
$N1: D2.3 (COMM), F2.2, R10.1, R11.2, R13.2, R14.2, R15.2
$N2: D4.3 (COMM), F4.2, R26.2, U3.8 (3Y), U3.11 (4Y)
$N3: D1.3 (COMM), F1.2, R1.1, R2.2, R4.2, R5.2, R6.2
$N101: D3.3 (COMM), F3.2, R19.2, U3.3 (1Y), U3.6 (2Y)
+1V8_ISO: C20.2, C34.2, C35.2, C50.2, C51.2, C55.2, C56.2, J4.2, L1.2, L2.1, L3.2, R72.1, R73.1, R74.1, TP22.1, U7.D1 (VOUT1), U7.E1 (VOUT1), U12.3 (VDDSSCG), U12.17 (VDDD), U12.36 (VDDR)
+3V3: C1.1, C3.1, C8.+, C9.2, C10.2, C12.2, C13.2, C14.2, C15.2, C18.2, C25.2, C26.2, C27.2, C28.2, C33.2, C42.2, C43.2, C44.2, C45.2, C46.2, C47.2, C49.2, C60.2, C63.2, C71.2, C72.2, C73.2, C74.2, C75.2, C81.2, FMC_LPC.P$116 (3P3V2), FMC_LPC.P$118 (3P3V3), FMC_LPC.P$120 (3P3V4), FMC_LPC.P$159 (3P3V1), J3.2, R20.2, R21.2, R22.2, R27.2, R28.2, R32.2, R33.2, TP10.1, TP11.1, U1.5 (V+), U2.5 (V+), U3.14 (VCC), U4.1 (VDD), U4.2 (REFA), U5.1 (VDD1), U8.21 (VCC), U8.22 (END), U8.25 (ENC), U8.29 (DVCC), U8.33 (ENB), U8.36 (ENA), U8.37 (VCC), U9.P10 (EN2), U9.P16 (VDD2), U10.P10 (EN2), U10.P16 (VDD2), U11.2 (VCC), U11.3 (VCC), U11.5 (ENA), U11.10 (ENB), U11.16 (VCC), U11.17 (VCC), U11.23 (ENC), U11.28 (END), U11.30 (VCC), U11.31 (VCC), U13.P10 (EN2), U13.P16 (VDD2), U14.P10 (EN2), U14.P16 (VDD2), U16.1 (EN1,2), U16.4 (VCC), U16.8 (EN3,4), U17.P1 (VDD1), U18.P10 (EN2), U18.P16 (VDD2)
+3V3_ISO: C17.2, C19.2, C32.2, C48.2, C59.2, C62.2, C64.2, C65.2, C66.2, C67.2, C68.2, C69.2, C70.2, C80.2, J4.3, R30.2, R31.2, R36.2, R56.1, R61.2, R62.2, R63.2, R65.2, R66.2, TP23.1, U5.8 (VDD2), U7.A1 (VOUT2), U7.B1 (VOUT2), U9.P1 (VDD1), U10.P1 (VDD1), U12.7 (VDDIO3), U12.20 (VDDIO2), U12.29 (VDDIO1), U13.P1 (VDD1), U14.P1 (VDD1), U17.P10 (EN2), U17.P16 (VDD2), U18.P1 (VDD1), U18.P7 (EN1)
+3V3_ISO_PG: U11.27 (D4A), U14.P11 (VOD)
+3V3_ISO_PG_ISO: R34.2, U7.D4 (PGOOD1), U14.P6 (VID)
+3V3_ISO_PG_N: FMC_LPC.P$107 (LA26_N), U11.33 (D4Z)
+3V3_ISO_PG_P: FMC_LPC.P$106 (LA26_P), U11.34 (D4Y)
+5.5V_ISO: C22.2, C23.+, C24.+, C31.2, C77.1, C79.2, L4.1, TP24.1, U6.3 (+VO), U7.A2 (VIN), U7.B2 (RUN2), U7.B3 (VIN), U7.D2 (RUN1), U7.D3 (VIN), U7.E2 (VIN)
+12V_ATX: C11.+, C21.+, L7/0R.1, PCIE-PWR.1, PCIE-PWR.2, PCIE-PWR.3, TP13.1
+12V_FPGA: C5.+, C6.2, C7.2, FMC_LPC.P$155 (12P0V1), FMC_LPC.P$157 (12P0V2), J3.3, R24.2, R25.2, TP12.1
BIAS_DI0: J1.1, U4.3 (VOUT0)
BIAS_DI1: J2.1, U4.4 (VOUT1)
BISTEN: R65.1, U12.6 (BISTEN), U15.1
D0: U9.P14 (VOA), U11.6 (A1A)
D0_ISO: R55.1, U9.P3 (VIA)
D0_N: FMC_LPC.P$98 (LA13_N), U11.63 (A1Z)
D0_P: FMC_LPC.P$97 (LA13_P), U11.64 (A1Y)
D1: U9.P13 (VOB), U11.7 (A2A)
D1_ISO: R54.1, U9.P4 (VIB)
D1_N: FMC_LPC.P$17 (LA11_N), U11.61 (A2Z)
D1_P: FMC_LPC.P$16 (LA11_P), U11.62 (A2Y)
D2: U9.P12 (VOC), U11.8 (A3A)
D2_ISO: R53.1, U9.P5 (VIC)
D2_N: FMC_LPC.P$56 (LA12_N), U11.59 (A3Z)
D2_P: FMC_LPC.P$55 (LA12_P), U11.60 (A3Y)
D3: U9.P11 (VOD), U11.9 (A4A)
D3_ISO: R52.1, U9.P6 (VID)
D3_N: FMC_LPC.P$135 (LA10_N), U11.57 (A4Z)
D3_P: FMC_LPC.P$134 (LA10_P), U11.58 (A4Y)
D4: U10.P14 (VOA), U11.11 (B1A)
D4_ISO: R51.1, U10.P3 (VIA)
D4_N: FMC_LPC.P$95 (LA09_N), U11.55 (B1Z)
D4_P: FMC_LPC.P$94 (LA09_P), U11.56 (B1Y)
D5: U10.P13 (VOB), U11.12 (B2A)
D5_ISO: R50.1, U10.P4 (VIB)
D5_N: FMC_LPC.P$14 (LA07_N), U11.53 (B2Z)
D5_P: FMC_LPC.P$13 (LA07_P), U11.54 (B2Y)
D6: U10.P12 (VOC), U11.13 (B3A)
D6_ISO: R49.1, U10.P5 (VIC)
D6_N: FMC_LPC.P$53 (LA08_N), U11.51 (B3Z)
D6_P: FMC_LPC.P$52 (LA08_P), U11.52 (B3Y)
D7: U10.P11 (VOD), U11.14 (B4A)
D7_ISO: R48.1, U10.P6 (VID)
D7_N: FMC_LPC.P$92 (LA05_N), U11.49 (B4Z)
D7_P: FMC_LPC.P$91 (LA05_P), U11.50 (B4Y)
D8: U11.19 (C1A), U13.P14 (VOA)
D8_ISO: R47.1, U13.P3 (VIA)
D8_N: FMC_LPC.P$11 (LA04_N), U11.47 (C1Z)
D8_P: FMC_LPC.P$10 (LA04_P), U11.48 (C1Y)
D9: U11.20 (C2A), U13.P13 (VOB)
D9_ISO: R46.1, U13.P4 (VIB)
D9_N: FMC_LPC.P$131 (LA06_N), U11.45 (C2Z)
D9_P: FMC_LPC.P$130 (LA06_P), U11.46 (C2Y)
D10: U11.21 (C3A), U13.P12 (VOC)
D10_ISO: R45.1, U13.P5 (VIC)
D10_N: FMC_LPC.P$50 (LA03_N), U11.43 (C3Z)
D10_P: FMC_LPC.P$49 (LA03_P), U11.44 (C3Y)
D11: U11.22 (C4A), U13.P11 (VOD)
D11_ISO: R44.1, U13.P6 (VID)
D11_N: FMC_LPC.P$8 (LA02_N), U11.41 (C4Z)
D11_P: FMC_LPC.P$7 (LA02_P), U11.42 (C4Y)
DES_GPIO0: U8.23 (D2Y), U17.P6 (VID)
DES_GPIO0_ISO: R60.1, U17.P11 (VOD)
DES_GPIO0_N: FMC_LPC.P$65 (LA22_N), U8.19 (D2B)
DES_GPIO0_P: FMC_LPC.P$64 (LA22_P), U8.18 (D2A)
DES_GPIO1: U8.24 (D1Y), U17.P5 (VIC)
DES_GPIO1_ISO: R59.1, U17.P12 (VOC)
DES_GPIO1_N: FMC_LPC.P$23 (LA19_N), U8.17 (D1B)
DES_GPIO1_P: FMC_LPC.P$22 (LA19_P), U8.16 (D1A)
DES_GPIO2: U8.26 (C2Y), U17.P4 (VIB)
DES_GPIO2_ISO: R58.1, U17.P13 (VOB)
DES_GPIO2_N: FMC_LPC.P$62 (LA20_N), U8.14 (C2B)
DES_GPIO2_P: FMC_LPC.P$61 (LA20_P), U8.13 (C2A)
DES_GPIO3: U8.27 (C1Y), U17.P3 (VIA)
DES_GPIO3_ISO: R57.1, U17.P14 (VOA)
DES_GPIO3_N: FMC_LPC.P$143 (LA18_N_CC), U8.12 (C1B)
DES_GPIO3_P: FMC_LPC.P$142 (LA18_P_CC), U8.11 (C1A)
DI0: TP2.TP, U1.1 (OUT), U16.2 (1A)
DI0_N: FMC_LPC.P$68 (LA25_N), U16.15 (1Z)
DI0_P: FMC_LPC.P$67 (LA25_P), U16.16 (1Y)
DI0_TERM: R7.1, R8.1, U8.35 (A1Y)
DI0_TERM_N: FMC_LPC.P$139 (LA1N_N), U8.2 (A1B)
DI0_TERM_P: FMC_LPC.P$138 (LA14_P), U8.1 (A1A)
DI1: TP1.TP, U2.1 (OUT), U16.3 (2A)
DI1_N: FMC_LPC.P$29 (LA24_N), U16.13 (2Z)
DI1_P: FMC_LPC.P$28 (LA24_P), U16.14 (2Y)
DI1_TERM: R16.1, R17.1, U8.34 (A2Y)
DI1_TERM_N: FMC_LPC.P$59 (LA16_N), U8.4 (A2B)
DI1_TERM_P: FMC_LPC.P$58 (LA16_P), U8.3 (A2A)
DO0: U3.2 (1A), U3.5 (2A), U8.31 (B2Y)
DO0_N: FMC_LPC.P$101 (LA17_N_CC), U8.9 (B2B)
DO0_P: FMC_LPC.P$100 (LA17_P_CC), U8.8 (B2A)
DO1: U3.9 (3A), U3.12 (4A), U8.32 (B1Y)
DO1_N: FMC_LPC.P$20 (LA15_N), U8.7 (B1B)
DO1_P: FMC_LPC.P$19 (LA15_P), U8.6 (B1A)
DOUTP_F: C57.2, L5.2, LINK.CLK (1), R70.2; also elsewhere on the board
GND: C1.2, C2.2, C3.2, C4.2, C5.-, C6.1, C7.1, C8.-, C9.1, C10.1, C11.-, C12.1, C13.1, C14.1, C15.1, C16.1, C18.1, C21.-, C25.1, C26.1, C27.1, C28.1, C33.1, C42.1, C43.1, C44.1, C45.1, C46.1, C47.1, C49.1, C60.1, C63.1, C71.1, C72.1, C73.1, C74.1, C75.1, C81.1, D1.1 (A), D2.1 (A), D3.1 (A), D4.1 (A), D5.2 (A), D6.A, DI1.GND$1 (2), DI1.GND$2 (2), DI1.GND$3 (2), DI1.GND$4 (2), DI2.GND$1 (2), DO1.GND$1 (2), DO1.GND$2 (2), DO1.GND$3 (2), DO1.GND$4 (2), DO2.GND$1 (2), FMC_LPC.GNDA (GND), FMC_LPC.GNDB (GND), FMC_LPC.P$3 (GND), FMC_LPC.P$6 (GND), FMC_LPC.P$9 (GND), FMC_LPC.P$12 (GND), FMC_LPC.P$15 (GND), FMC_LPC.P$18 (GND), FMC_LPC.P$21 (GND), FMC_LPC.P$24 (GND), FMC_LPC.P$27 (GND), FMC_LPC.P$30 (GND), FMC_LPC.P$33 (GND), FMC_LPC.P$36 (GND), FMC_LPC.P$39 (GND), FMC_LPC.P$41 (GND), FMC_LPC.P$44 (GND), FMC_LPC.P$45 (GND), FMC_LPC.P$48 (GND), FMC_LPC.P$51 (GND), FMC_LPC.P$54 (GND), FMC_LPC.P$57 (GND), FMC_LPC.P$60 (GND), FMC_LPC.P$63 (GND42), FMC_LPC.P$66 (GND), FMC_LPC.P$69 (GND), FMC_LPC.P$72 (GND), FMC_LPC.P$75 (GND), FMC_LPC.P$78 (GND), FMC_LPC.P$80 (GND), FMC_LPC.P$82 (GND), FMC_LPC.P$83 (GND), FMC_LPC.P$86 (GND), FMC_LPC.P$87 (GND), FMC_LPC.P$90 (GND), FMC_LPC.P$93 (GND), FMC_LPC.P$96 (GND), FMC_LPC.P$99 (GND), FMC_LPC.P$102 (GND), FMC_LPC.P$105 (GND), FMC_LPC.P$108 (GND), FMC_LPC.P$117 (GND), FMC_LPC.P$119 (GND), FMC_LPC.P$121 (GND), FMC_LPC.P$124 (GND), FMC_LPC.P$125 (GND), FMC_LPC.P$128 (GND), FMC_LPC.P$129 (GND), FMC_LPC.P$132 (GND), FMC_LPC.P$133 (GND), FMC_LPC.P$136 (GND), FMC_LPC.P$137 (GND), FMC_LPC.P$140 (GND), FMC_LPC.P$141 (GND), FMC_LPC.P$144 (GND), FMC_LPC.P$145 (GND), FMC_LPC.P$148 (GND), FMC_LPC.P$149 (GND), FMC_LPC.P$152 (GND), FMC_LPC.P$153 (GND), FMC_LPC.P$156 (GND), FMC_LPC.P$158 (GND19), FMC_LPC.P$160 (GND), J3.1, J3.4, J6.G1 (2), J6.G2 (2), J6.G3 (2), J6.G4 (2), J8.G1 (2), J8.G2 (2), J8.G3 (2), J8.G4 (2), PCIE-PWR.4, PCIE-PWR.5, PCIE-PWR.6, Q1.S, Q2.S, Q3.S, Q4.S, R2.1, R9.1, R11.1, R18.1, R23.1, R29.1, TERM.C1 (C), TERM.C2 (C), TP3.1, TP4.1, TP5.1, TP6.1, TP7.1, TP8.1, TP9.1, TP18.1, U1.2 (V-), U2.2 (V-), U3.7 (GND), U4.5 (AVSS), U4.6 (LAT/HVC), U5.4 (GND1), U6.2 (GND), U8.5 (AGND), U8.10 (AGND), U8.15 (AGND), U8.20 (GND), U8.28 (DGND), U8.30 (DGND), U8.38 (GND), U9.P9 (GND2), U9.P15 (GND2), U10.P9 (GND2), U10.P15 (GND2), U11.1 (GND), U11.4 (GND), U11.15 (GND), U11.18 (GND), U11.29 (GND), U11.32 (GND), U13.P9 (GND2), U13.P15 (GND2), U14.P9 (GND2), U14.P15 (GND2), U16.5 (GND), U17.P2 (GND1), U17.P8 (GND1), U18.P9 (GND2), U18.P15 (GND2); also elsewhere on the board
GND_ISO: C17.1, C19.1, C20.1, C22.1, C23.-, C24.-, C29.1, C30.1, C31.1, C32.1, C34.1, C35.1, C36.1, C37.1, C38.1, C39.1, C40.1, C41.1, C48.1, C50.1, C51.1, C52.1, C53.1, C54.1, C55.1, C56.1, C59.1, C61.1, C62.1, C64.1, C65.1, C66.1, C67.1, C68.1, C69.1, C70.1, C76.2, C77.2, C78.1, C79.1, C80.1, J4.1, J4.4, J5.G1 (2), J5.G2 (2), J5.G3 (2), J5.G4 (2), J7.G1 (2), J7.G2 (2), J7.G3 (2), J7.G4 (2), LINK.GND$1 (2), LINK.GND$2 (2), LINK.GND$3 (2), LINK.GND$4 (2), PWR/LOCK.C1 (C), Q5.S, Q6.S, R35.2, R37.2, R38.2, R39.2, R42.2, R67.1, R69.1, R75.2, R76.2, R77.2, S1.A, TP17.1, TP21.1, TP25.1, TP26.1, U5.5 (GND2), U6.5 (-VO), U7.B5 (GND), U7.C1 (GND), U7.C2 (GND), U7.C5 (SYNC/MODE), U7.D5 (GND), U9.P2 (GND1), U9.P8 (GND1), U10.P2 (GND1), U10.P8 (GND1), U12.43 (RES), U12.44 (TESTEN), U12.49 (DAP), U13.P2 (GND1), U13.P8 (GND1), U14.P2 (GND1), U14.P8 (GND1), U15.5, U15.6, U15.7, U15.8, U17.P9 (GND2), U17.P15 (GND2), U18.P2 (GND1), U18.P8 (GND1); also elsewhere on the board
GPI0_N: FMC_LPC.P$26 (LA21_N), U16.9 (4Z)
GPI0_P: FMC_LPC.P$25 (LA21_P), U16.10 (4Y)
GPI1_N: FMC_LPC.P$104 (LA23_N), U16.11 (3Z)
GPI1_P: FMC_LPC.P$103 (LA23_P), U16.12 (3Y)
HSYNC: U11.24 (D1A), U14.P14 (VOA)
HSYNC_ISO: R43.1, U14.P3 (VIA)
HSYNC_N: FMC_LPC.P$89 (LA01_N_CC), U11.39 (D1Z)
HSYNC_P: FMC_LPC.P$88 (LA01_P_CC), U11.40 (D1Y)
IDX0: R72.2, R75.1, U12.35 (IDX0)
IDX1: R73.2, R76.1, U12.34 (IDX1)
INTVCC: R34.1, U7.C3 (INTVCC)
LOCK: U16.6 (3A), U18.P14 (VOA)
LOCK_ISO: R68.2, U12.48 (LOCK), U18.P3 (VIA)
MODE: R74.2, R77.1, U12.37 (MODE)
unnamed: Q5.G, R64.1, R67.2
unnamed: Q1.D, R4.1, R5.1, R6.1
unnamed: R1.2, U1.3 (+IN)
unnamed: R40.2, U12.8 (PCLK)
unnamed: R39.1, U7.A4 (FB2)
unnamed: Q2.D, R13.1, R14.1, R15.1
unnamed: C29.2, U7.A3 (TRACK/SS2)
unnamed: R17.2, TERM.A1 (A)
unnamed: R37.1, U7.E4 (FB1)
unnamed: C30.2, U7.E3 (TRACK/SS1)
unnamed: R41.2, U12.9 (VSYNC)
unnamed: PWR/LOCK.A2 (A), R66.1
unnamed: R43.2, U12.10 (HSYNC)
unnamed: C2.1, R3.2, U1.4 (-IN)
unnamed: R10.2, U2.3 (+IN)
unnamed: C4.1, R12.2, U2.4 (-IN)
unnamed: L5.1, L6.2, R70.1, R71.2
unnamed: C76.1, C78.2, L4.2, L6.1, R71.1
unnamed: OUT.A1 (A), R20.1
unnamed: R21.1, U3.1 (~1G), U3.4 (~2G)
unnamed: R22.1, U3.10 (~3G), U3.13 (~4G)
unnamed: R35.1, U6.4 (TRIM)
unnamed: C57.1, U12.41 (RIN0+)
unnamed: C58.1, U12.42 (RIN0-)
unnamed: PWR/LOCK.C2 (C), Q6.D
unnamed: R8.2, TERM.A2 (A)
unnamed: OUT.A2 (A), R28.1
unnamed: C58.2, R42.1
unnamed: PWR/LOCK.A1 (A), R36.1
unnamed: Q2.G, R16.2, R18.2
unnamed: OUT.C1 (C), Q3.D
unnamed: J2.2, R12.1
unnamed: Q1.G, R7.2, R9.2
unnamed: R57.2, U12.25 (GPIO3)
unnamed: Q3.G, R19.1, R23.2
unnamed: J7.SIG (1), R79.1
unnamed: R46.2, U12.13 (ROUT9)
unnamed: R47.2, U12.14 (ROUT8)
unnamed: R48.2, U12.15 (ROUT7)
unnamed: R49.2, U12.16 (ROUT6)
unnamed: R50.2, U12.18 (ROUT5)
unnamed: R51.2, U12.19 (ROUT4)
unnamed: R52.2, U12.21 (ROUT3)
unnamed: R53.2, U12.22 (ROUT2)
unnamed: R54.2, U12.23 (ROUT1)
unnamed: R55.2, U12.24 (ROUT0)
unnamed: R44.2, U12.11 (ROUT11)
unnamed: R45.2, U12.12 (ROUT10)
unnamed: R78.1, U18.P5 (VIC)
unnamed: R58.2, U12.26 (GPIO2)
unnamed: R59.2, U12.27 (GPIO1)
unnamed: R60.2, U12.28 (GPIO0)
unnamed: OUT.C2 (C), Q4.D
unnamed: Q4.G, R26.1, R29.2
unnamed: Q6.G, R68.1, R69.2
unnamed: J1.2, R3.1
unnamed: R38.1, U7.C4 (FREQ)
OEN: R63.1, U12.5 (OEN), U15.2
OSS_SEL: R62.1, U12.4 (OSS_SEL), U15.3
PASS: U16.7 (4A), U18.P12 (VOC)
PASS_ISO: R78.2, U12.47 (PASS)
PCLK: U11.26 (D3A), U14.P12 (VOC)
PCLK_ISO: R40.1, U14.P5 (VIC)
PCLK_N: FMC_LPC.P$43 (CLK1_M2C_N), U11.35 (D3Z)
PCLK_P: FMC_LPC.P$42 (CLK1_M2C_P), U11.36 (D3Y)
PDN_ISO: C61.2, Q5.D, R56.2, R64.2, R80.2, S1.B (S), U12.30 (PDN)
SCL: FMC_LPC.P$150 (SCL), R33.1, TP20.1, U4.7 (SCL), U5.3 (SCL1)
SCL_ISO: R30.1, TP15.1, U5.6 (SCL2), U12.2 (SCL)
SDA: FMC_LPC.P$151 (SDA), R32.1, TP19.1, U4.8 (SDA), U5.2 (SDA1)
SDA_ISO: R31.1, TP16.1, U5.7 (SDA2), U12.1 (SDA)
SEL: R61.1, U12.46 (SEL), U15.4
SMA_IN: FMC_LPC.P$146 (LA27_P), J6.SIG (1), U18.P13 (VOB)
SMA_IN_ISO: J5.SIG (1), U18.P4 (VIB)
SMA_OUT: FMC_LPC.P$147 (LA27_N), J8.SIG (1), U18.P11 (VID)
SMA_OUT_ISO: R79.2, R80.1, U18.P6 (VOD)
TDI-TDO: FMC_LPC.P$110 (TDI), FMC_LPC.P$111 (TDO)
VDDCML0: C52.2, C53.2, C54.2, L3.1, U12.40 (VDDCML0)
VDDCML1: C36.2, C37.2, C38.2, L1.1, U12.31 (VDDCML1)
VDDPLL: C39.2, C40.2, C41.2, L2.2, U12.45 (VDDPLL)
VIN: L7/0R.2, U6.1 (VIN), U6.6 (EN)
VSYNC: U11.25 (D2A), U14.P13 (VOB)
VSYNC_ISO: R41.1, U14.P4 (VIB)
VSYNC_N: FMC_LPC.P$5 (CLK0_M2C_N), U11.37 (D2Z)
VSYNC_P: FMC_LPC.P$4 (CLK0_M2C_P), U11.38 (D2Y)
V_PROTECT: C16.2, D1.2 (C), D2.2 (C), D3.2 (C), D4.2 (C), D6.C, R24.1, R25.1, TP14.1

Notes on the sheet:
HEADSTAGE SIDE
AQ. BOARD SIDE
ISOLATED TEST POINTS
POWER INPUT
FMC HEADER
PCI ADD IN CARD
INPUT PROTECTION BIAS VOLTAGE ~4.6V
IMMEDIATE INPUT OVERVOLTAGE PROTECTION
NOTES: - ISO7240 Zo for 3.3V is ~100 Ohms.
L2 is the smallest package size I could find that barely meets current saturation requriements. An 8x8mm device that is probably safer is the Bourns SRN8040TA series.
UEI15 Choices: 12V: S24SE12002 w/ Rtrim = Inf 5.5V: UEI15-050-Q12P-C w/ Rtrm = 9.53k resistor
Power: ~1.3A DC at 12V; 15.6W. With 90% efficiency regulation to 5.5V at serializer, this translates to 2.55A available, which is enough for 1A/LED + 500 mA serializer and FPGA.
LVCMOS1.8
Seeed 4 layer stackup: 1.4 mil trace 8 mil prepeg 0.7 mil trace XX mil FR4 core 0.7 mil trace 8 mil prepeg 1.4 mil trace
SN65LVDT388A has integrated 110 ohm term resistors.
Parity error on high-speed forward channel and pass will go low. This should be provided to LPC connector
DI0, DI1, PASS, LOCK
DNP

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

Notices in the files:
pcie-analog-io/pcie-host.brd:
CC BY-SA-4.0
pcie-analog-io/pcie-host.sch:
LICENSE: CC-BY-SA-4.0
pcie-host/pcie-host.brd:
CERN OHL v1.2
pcie-host/pcie-host.sch:
LICENSE: CERN OHL v1.2
